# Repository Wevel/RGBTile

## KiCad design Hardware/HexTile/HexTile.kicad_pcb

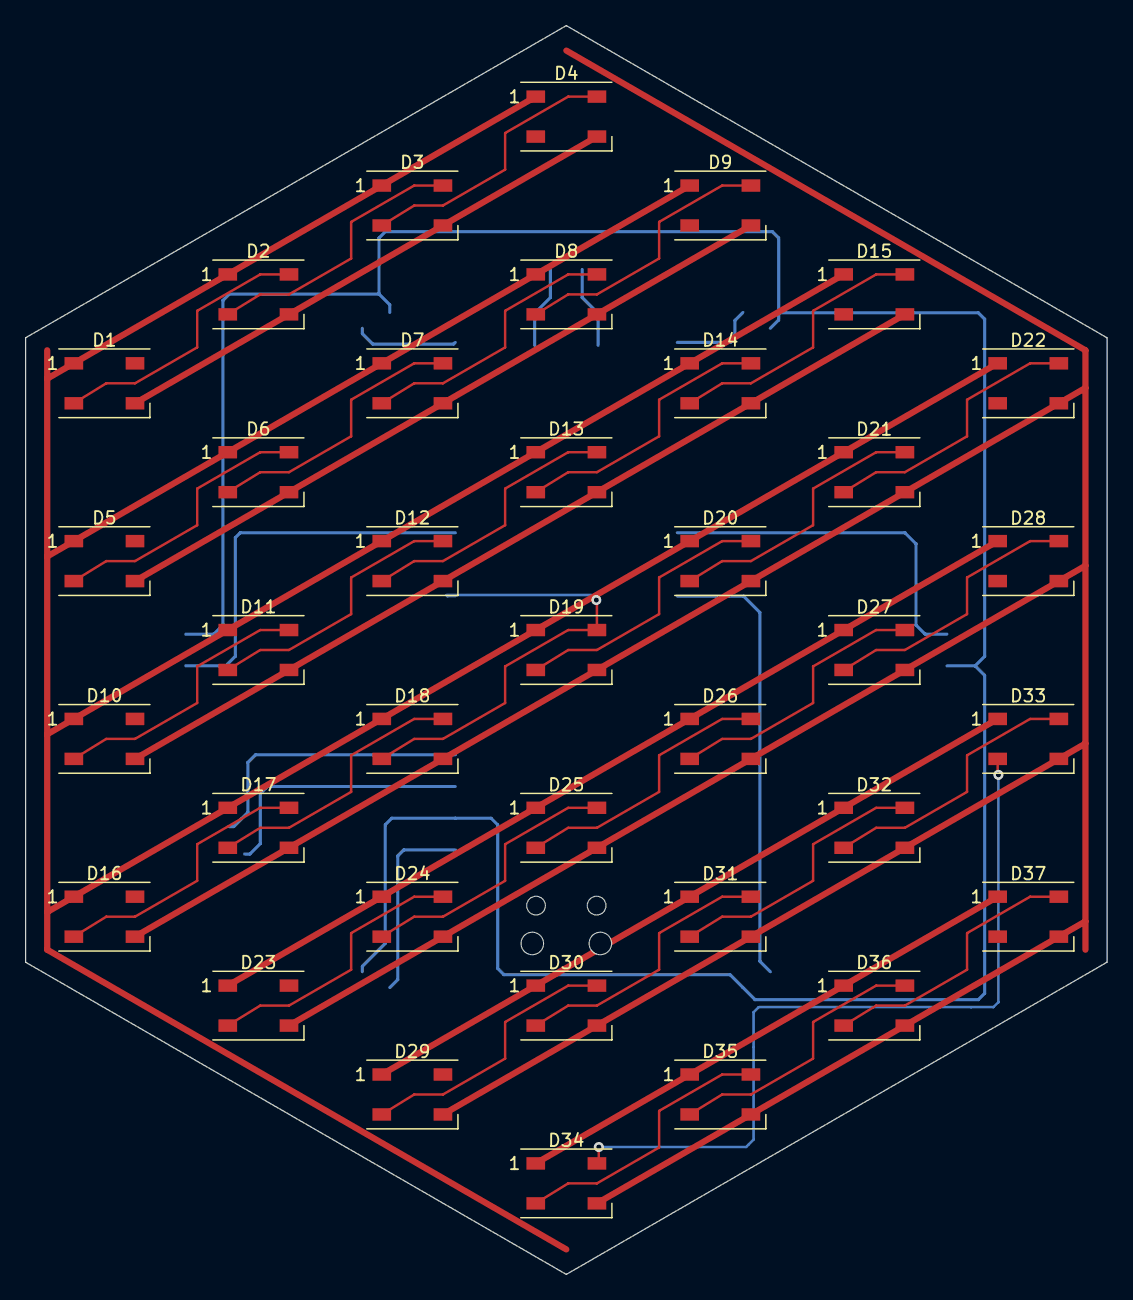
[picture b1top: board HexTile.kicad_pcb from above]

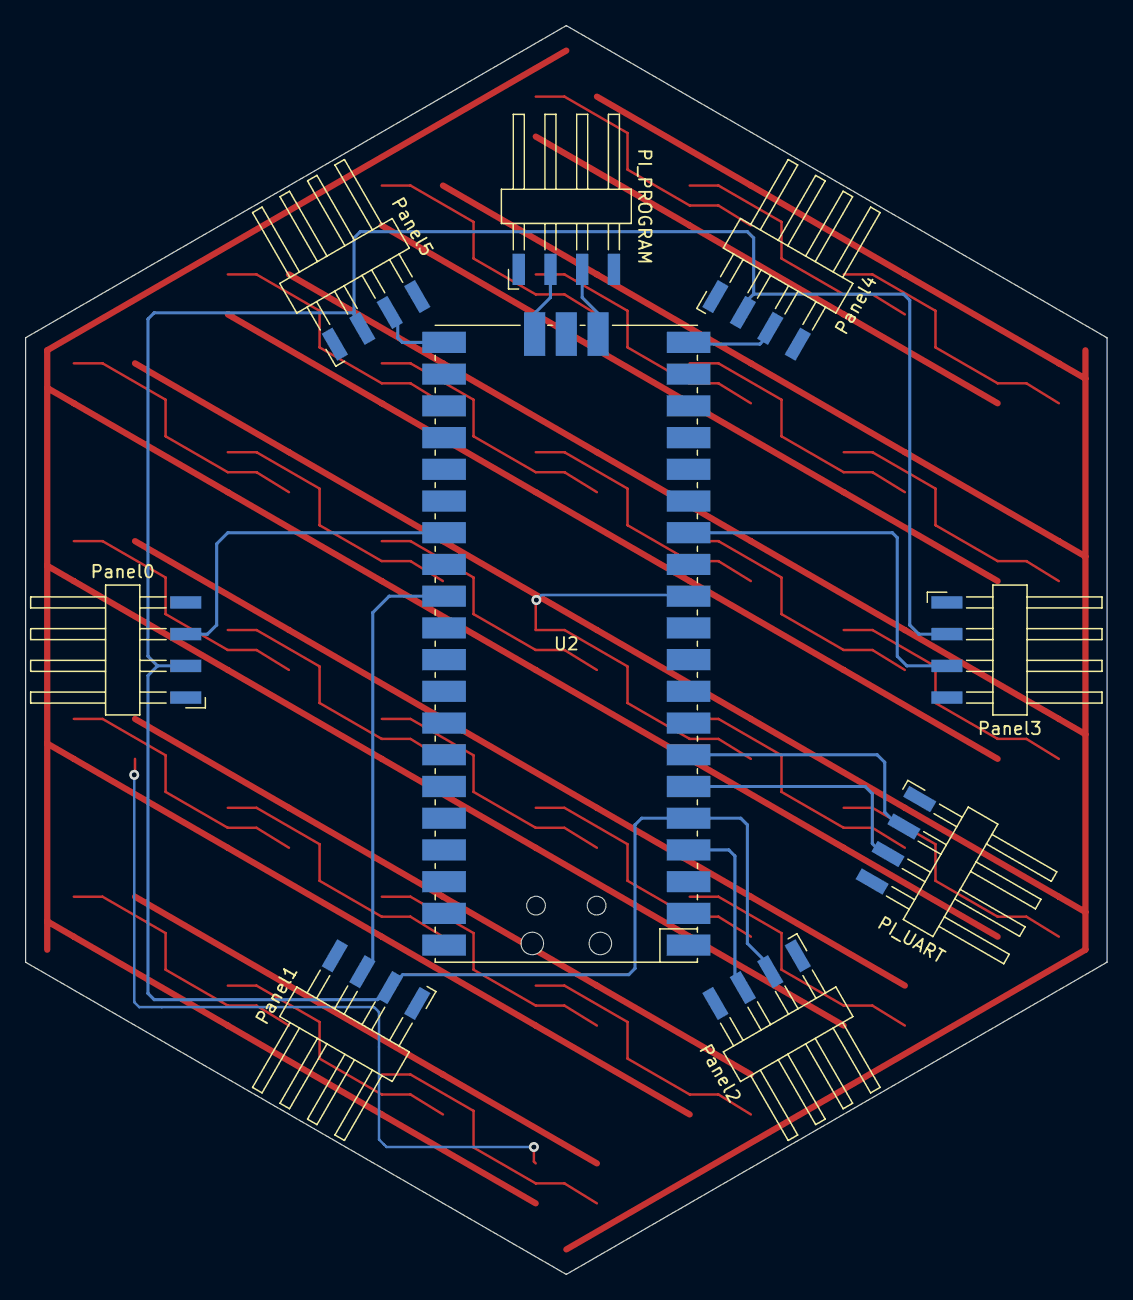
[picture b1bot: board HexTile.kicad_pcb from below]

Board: 2 copper layers, 86.6 x 100.0 mm, 46 parts (9 on the bottom side), 50 nets.

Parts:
D1, D2, D3, D4, D5, D6, D7, D8, D9, D10, D11, D12, D13, D14, D15, D16, D17, D18, D19, D20, D21, D22, D23, D24, D25, D26, D27, D28, D29, D30, D31, D32, D33, D34, D35, D36, D37: WS2812B; LED_WS2812B_PLCC4_5.0x5.0mm_P3.2mm
J1: Panel0; Harwin_M20-89004xx_1x04_P2.54mm_Horizontal
J2: Panel1; Harwin_M20-89004xx_1x04_P2.54mm_Horizontal
J3: Panel2; Harwin_M20-89004xx_1x04_P2.54mm_Horizontal
J4: Panel3; Harwin_M20-89004xx_1x04_P2.54mm_Horizontal
J5: Panel4; Harwin_M20-89004xx_1x04_P2.54mm_Horizontal
J6: Panel5; Harwin_M20-89004xx_1x04_P2.54mm_Horizontal
J7: PI_UART; Harwin_M20-89004xx_1x04_P2.54mm_Horizontal
J9: PI_PROGRAM; Harwin_M20-89004xx_1x04_P2.54mm_Horizontal
U2: Pico; RPi_Pico_SMD

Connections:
+5V: D1.1 (VDD), D2.1 (VDD), D3.1 (VDD), D4.1 (VDD), D5.1 (VDD), D6.1 (VDD), D7.1 (VDD), D8.1 (VDD), D9.1 (VDD), D10.1 (VDD), D11.1 (VDD), D12.1 (VDD), D13.1 (VDD), D14.1 (VDD), D15.1 (VDD), D16.1 (VDD), D17.1 (VDD), D18.1 (VDD), D19.1 (VDD), D20.1 (VDD), D21.1 (VDD), D22.1 (VDD), D23.1 (VDD), D24.1 (VDD), D25.1 (VDD), D26.1 (VDD), D27.1 (VDD), D28.1 (VDD), D29.1 (VDD), D30.1 (VDD), D31.1 (VDD), D32.1 (VDD), D33.1 (VDD), D34.1 (VDD), D35.1 (VDD), D36.1 (VDD), D37.1 (VDD), J1.4, J2.4, J3.4, J4.4, J5.4, J6.4, J7.4, J9.4, U2.39 (VSYS)
/LED_DATA: D1.4 (DIN), U2.12 (GPIO9)
/PI_Debug_UART_RX: J7.3, U2.6 (GPIO4)
/PI_Debug_UART_TX: J7.2, U2.7 (GPIO5)
/PI_SWCLK: J9.3, U2.41 (SWCLK)
/PI_SWDIO: J9.2, U2.43 (SWDIO)
/Panel_UART_RX_0: J1.3, U2.27 (GPIO21)
/Panel_UART_RX_1: J2.3, U2.29 (GPIO22)
/Panel_UART_RX_2: J3.3, U2.4 (GPIO2)
/Panel_UART_RX_3: J4.3, U2.14 (GPIO10)
/Panel_UART_RX_4: J5.3, U2.20 (GPIO15)
/Panel_UART_RX_5: J6.3, U2.21 (GPIO16)
/Panel_UART_TX: J1.2, J2.2, J3.2, J4.2, J5.2, J6.2, U2.5 (GPIO3)
GND: D1.3 (VSS), D2.3 (VSS), D3.3 (VSS), D4.3 (VSS), D5.3 (VSS), D6.3 (VSS), D7.3 (VSS), D8.3 (VSS), D9.3 (VSS), D10.3 (VSS), D11.3 (VSS), D12.3 (VSS), D13.3 (VSS), D14.3 (VSS), D15.3 (VSS), D16.3 (VSS), D17.3 (VSS), D18.3 (VSS), D19.3 (VSS), D20.3 (VSS), D21.3 (VSS), D22.3 (VSS), D23.3 (VSS), D24.3 (VSS), D25.3 (VSS), D26.3 (VSS), D27.3 (VSS), D28.3 (VSS), D29.3 (VSS), D30.3 (VSS), D31.3 (VSS), D32.3 (VSS), D33.3 (VSS), D34.3 (VSS), D35.3 (VSS), D36.3 (VSS), D37.3 (VSS), J1.1, J2.1, J3.1, J4.1, J5.1, J6.1, J7.1, J9.1, U2.3 (GND), U2.8 (GND), U2.13 (GND), U2.18 (GND), U2.23 (GND), U2.28 (GND), U2.38 (GND), U2.42 (GND)
unnamed: D1.2 (DOUT), D2.4 (DIN)
unnamed: D2.2 (DOUT), D3.4 (DIN)
unnamed: D3.2 (DOUT), D4.4 (DIN)
unnamed: D4.2 (DOUT), D5.4 (DIN)
unnamed: D5.2 (DOUT), D6.4 (DIN)
unnamed: D6.2 (DOUT), D7.4 (DIN)
unnamed: D7.2 (DOUT), D8.4 (DIN)
unnamed: D8.2 (DOUT), D9.4 (DIN)
unnamed: D9.2 (DOUT), D10.4 (DIN)
unnamed: D10.2 (DOUT), D11.4 (DIN)
unnamed: D11.2 (DOUT), D12.4 (DIN)
unnamed: D12.2 (DOUT), D13.4 (DIN)
unnamed: D13.2 (DOUT), D14.4 (DIN)
unnamed: D14.2 (DOUT), D15.4 (DIN)
unnamed: D15.2 (DOUT), D16.4 (DIN)
unnamed: D16.2 (DOUT), D17.4 (DIN)
unnamed: D17.2 (DOUT), D18.4 (DIN)
unnamed: D18.2 (DOUT), D19.4 (DIN)
unnamed: D19.2 (DOUT), D20.4 (DIN)
unnamed: D20.2 (DOUT), D21.4 (DIN)
unnamed: D21.2 (DOUT), D22.4 (DIN)
unnamed: D22.2 (DOUT), D23.4 (DIN)
unnamed: D23.2 (DOUT), D24.4 (DIN)
unnamed: D24.2 (DOUT), D25.4 (DIN)
unnamed: D25.2 (DOUT), D26.4 (DIN)
unnamed: D26.2 (DOUT), D27.4 (DIN)
unnamed: D27.2 (DOUT), D28.4 (DIN)
unnamed: D28.2 (DOUT), D29.4 (DIN)
unnamed: D29.2 (DOUT), D30.4 (DIN)
unnamed: D30.2 (DOUT), D31.4 (DIN)
unnamed: D31.2 (DOUT), D32.4 (DIN)
unnamed: D32.2 (DOUT), D33.4 (DIN)
unnamed: D33.2 (DOUT), D34.4 (DIN)
unnamed: D34.2 (DOUT), D35.4 (DIN)
unnamed: D35.2 (DOUT), D36.4 (DIN)
unnamed: D36.2 (DOUT), D37.4 (DIN)

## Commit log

2022-12-22 Made some progress with routing.
